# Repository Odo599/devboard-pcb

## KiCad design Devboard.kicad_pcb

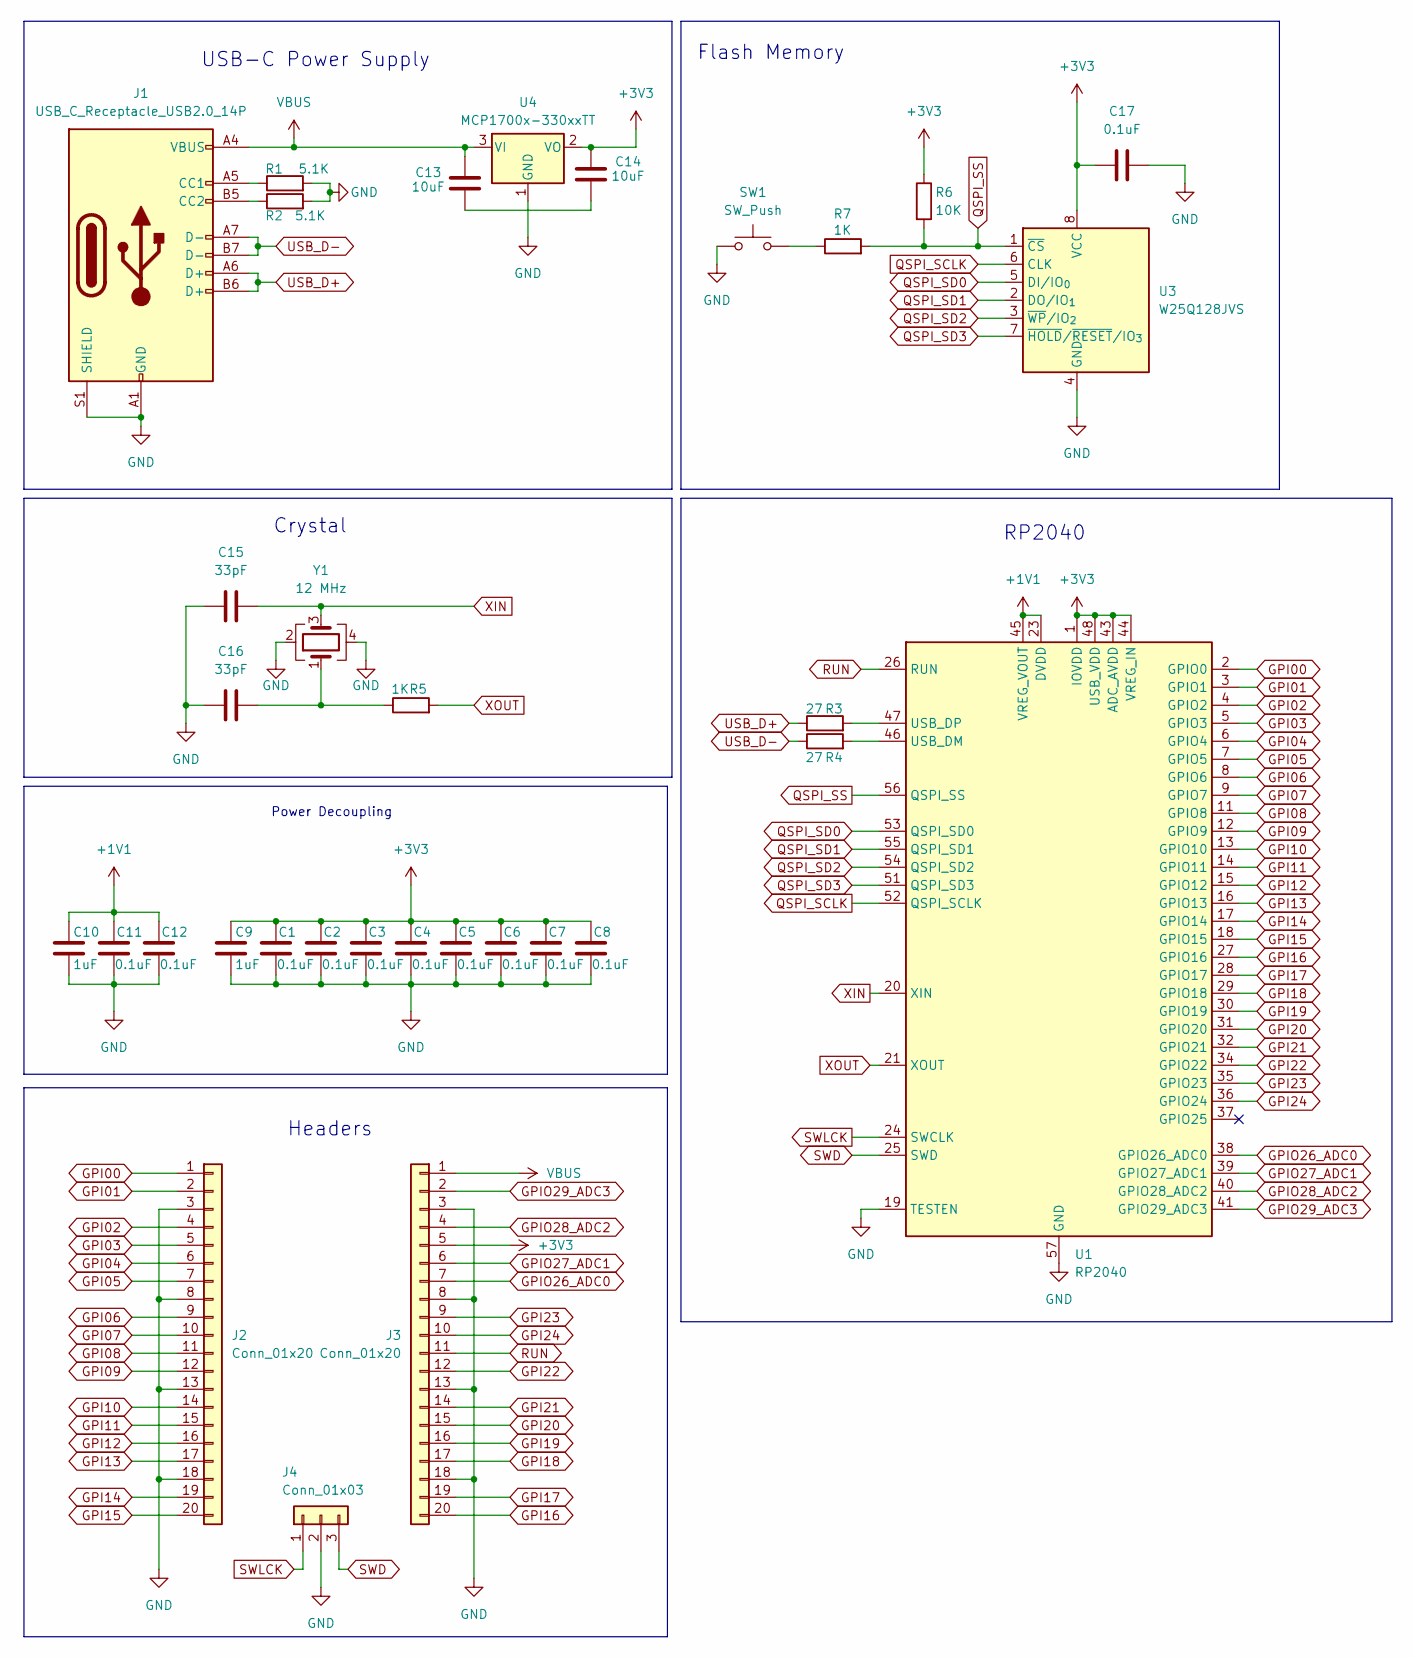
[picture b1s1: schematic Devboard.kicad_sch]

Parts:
C1, C2, C3, C4, C5, C6, C7, C8, C11, C12, C17: 0.1uF; C_0402_1005Metric
C9, C10: 1uF; C_0402_1005Metric
C13, C14: 10uF; C_0603_1608Metric
C15, C16: 33pF; C_0603_1608Metric
J1: USB_C_Receptacle_USB2.0_14P; USB_C_Receptacle_HRO_TYPE-C-31-M-12
J2, J3: Conn_01x20; PinHeader_1x20_P2.54mm_Vertical
J4: Conn_01x03; PinHeader_1x03_P2.54mm_Vertical
R1, R2: 5.1K; R_0402_1005Metric
R3, R4: 27; R_0402_1005Metric
R5, R7: 1K; R_0402_1005Metric
R6: 10K; R_0402_1005Metric
SW1: SW_Push; SW_Push_SPST_NO_Alps_SKRK
U1: RP2040; QFN-56-1EP_7x7mm_P0.4mm_EP3.2x3.2mm
U3: W25Q128JVS; SOIC-8_5.3x5.3mm_P1.27mm
U4: MCP1700x-330xxTT; SOT-23
Y1: 12 MHz; Crystal_SMD_3225-4Pin_3.2x2.5mm

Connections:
+1V1: C10.1, C11.1, C12.1, U1.23 (DVDD), U1.45 (VREG_VOUT), U1.50 (DVDD)
+3V3: C1.1, C2.1, C3.1, C4.1, C5.1, C6.1, C7.1, C8.1, C9.1, C14.1, C17.1, J3.5, R6.1, U1.1 (IOVDD), U1.10 (IOVDD), U1.22 (IOVDD), U1.33 (IOVDD), U1.42 (IOVDD), U1.43 (ADC_AVDD), U1.44 (VREG_IN), U1.48 (USB_VDD), U1.49 (IOVDD), U3.8 (VCC), U4.2 (VO)
GND: C1.2, C2.2, C3.2, C4.2, C5.2, C6.2, C7.2, C8.2, C9.2, C10.2, C11.2, C12.2, C15.1, C16.1, C17.2, J1.A1 (GND), J1.A12 (GND), J1.B1 (GND), J1.B12 (GND), J1.S1 (SHIELD), J2.3, J2.8, J2.13, J2.18, J3.3, J3.8, J3.13, J3.18, J4.2, R1.2, R2.2, SW1.1, U1.19 (TESTEN), U1.57 (GND), U3.4 (GND), U4.1 (GND), Y1.2, Y1.4
GPI00: J2.1, U1.2 (GPIO0)
GPI01: J2.2, U1.3 (GPIO1)
GPI02: J2.4, U1.4 (GPIO2)
GPI03: J2.5, U1.5 (GPIO3)
GPI04: J2.6, U1.6 (GPIO4)
GPI05: J2.7, U1.7 (GPIO5)
GPI06: J2.9, U1.8 (GPIO6)
GPI07: J2.10, U1.9 (GPIO7)
GPI08: J2.11, U1.11 (GPIO8)
GPI09: J2.12, U1.12 (GPIO9)
GPI10: J2.14, U1.13 (GPIO10)
GPI11: J2.15, U1.14 (GPIO11)
GPI12: J2.16, U1.15 (GPIO12)
GPI13: J2.17, U1.16 (GPIO13)
GPI14: J2.19, U1.17 (GPIO14)
GPI15: J2.20, U1.18 (GPIO15)
GPI16: J3.20, U1.27 (GPIO16)
GPI17: J3.19, U1.28 (GPIO17)
GPI18: J3.17, U1.29 (GPIO18)
GPI19: J3.16, U1.30 (GPIO19)
GPI20: J3.15, U1.31 (GPIO20)
GPI21: J3.14, U1.32 (GPIO21)
GPI22: J3.12, U1.34 (GPIO22)
GPI23: J3.9, U1.35 (GPIO23)
GPI24: J3.10, U1.36 (GPIO24)
GPIO26_ADC0: J3.7, U1.38 (GPIO26_ADC0)
GPIO27_ADC1: J3.6, U1.39 (GPIO27_ADC1)
GPIO28_ADC2: J3.4, U1.40 (GPIO28_ADC2)
GPIO29_ADC3: J3.2, U1.41 (GPIO29_ADC3)
unnamed: C13.2, C14.2
unnamed: C16.2, R5.1, Y1.1
unnamed: J1.A5 (CC1), R1.1
unnamed: J1.B5 (CC2), R2.1
unnamed: R7.1, SW1.2
unnamed: R4.2, U1.46 (USB_DM)
unnamed: R3.2, U1.47 (USB_DP)
QSPI_SCLK: U1.52 (QSPI_SCLK), U3.6 (CLK)
QSPI_SD0: U1.53 (QSPI_SD0), U3.5 (DI/IO_{0})
QSPI_SD1: U1.55 (QSPI_SD1), U3.2 (DO/IO_{1})
QSPI_SD2: U1.54 (QSPI_SD2), U3.3 (~WP/IO_{2})
QSPI_SD3: U1.51 (QSPI_SD3), U3.7 (~HOLD/~RESET/IO_{3})
QSPI_SS: R6.2, R7.2, U1.56 (QSPI_SS), U3.1 (~CS)
RUN: J3.11, U1.26 (RUN)
SWD: J4.3, U1.25 (SWD)
SWLCK: J4.1, U1.24 (SWCLK)
USB_D+: J1.A6 (D+), J1.B6 (D+), R3.1
USB_D-: J1.A7 (D-), J1.B7 (D-), R4.1
VBUS: C13.1, J1.A4 (VBUS), J1.A9 (VBUS), J1.B4 (VBUS), J1.B9 (VBUS), J3.1, U4.3 (VI)
XIN: C15.2, U1.20 (XIN), Y1.3
XOUT: R5.2, U1.21 (XOUT)

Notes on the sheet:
Flash Memory
RP2040
USB-C Power Supply
Headers
Crystal
Power Decoupling

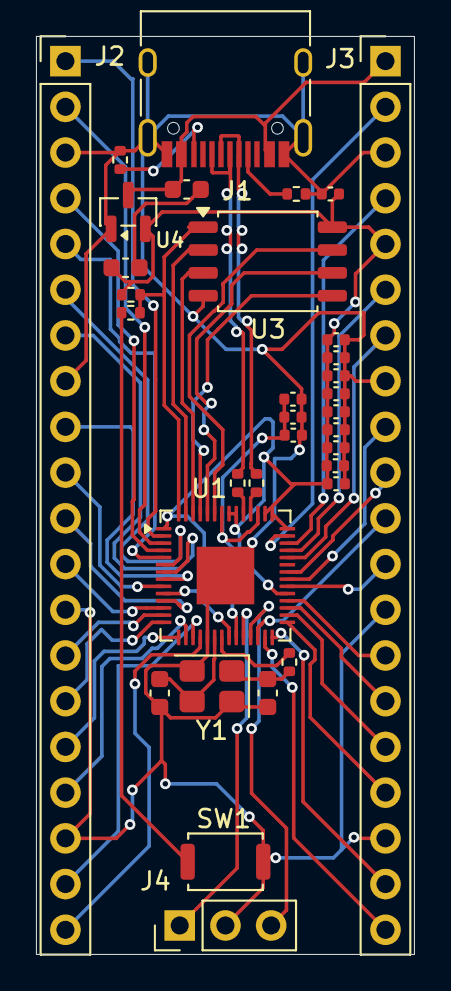
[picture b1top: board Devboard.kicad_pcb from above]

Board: 2 copper layers, 21.0 x 51.0 mm, 33 parts (0 on the bottom side), 53 nets.

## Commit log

2025-10-23 (Nearly) finished schematic
2025-10-23 Actually finished schematic
2025-10-23 Cleaned up schematics
2025-10-24 Finished routing the PCB
2025-10-24 Cleaned up silkscreen
